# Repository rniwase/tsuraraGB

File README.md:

# tsuraraGB
Nintendo Gameboy cartridge-shaped FPGA (Lattice iCE40UP5K) development board

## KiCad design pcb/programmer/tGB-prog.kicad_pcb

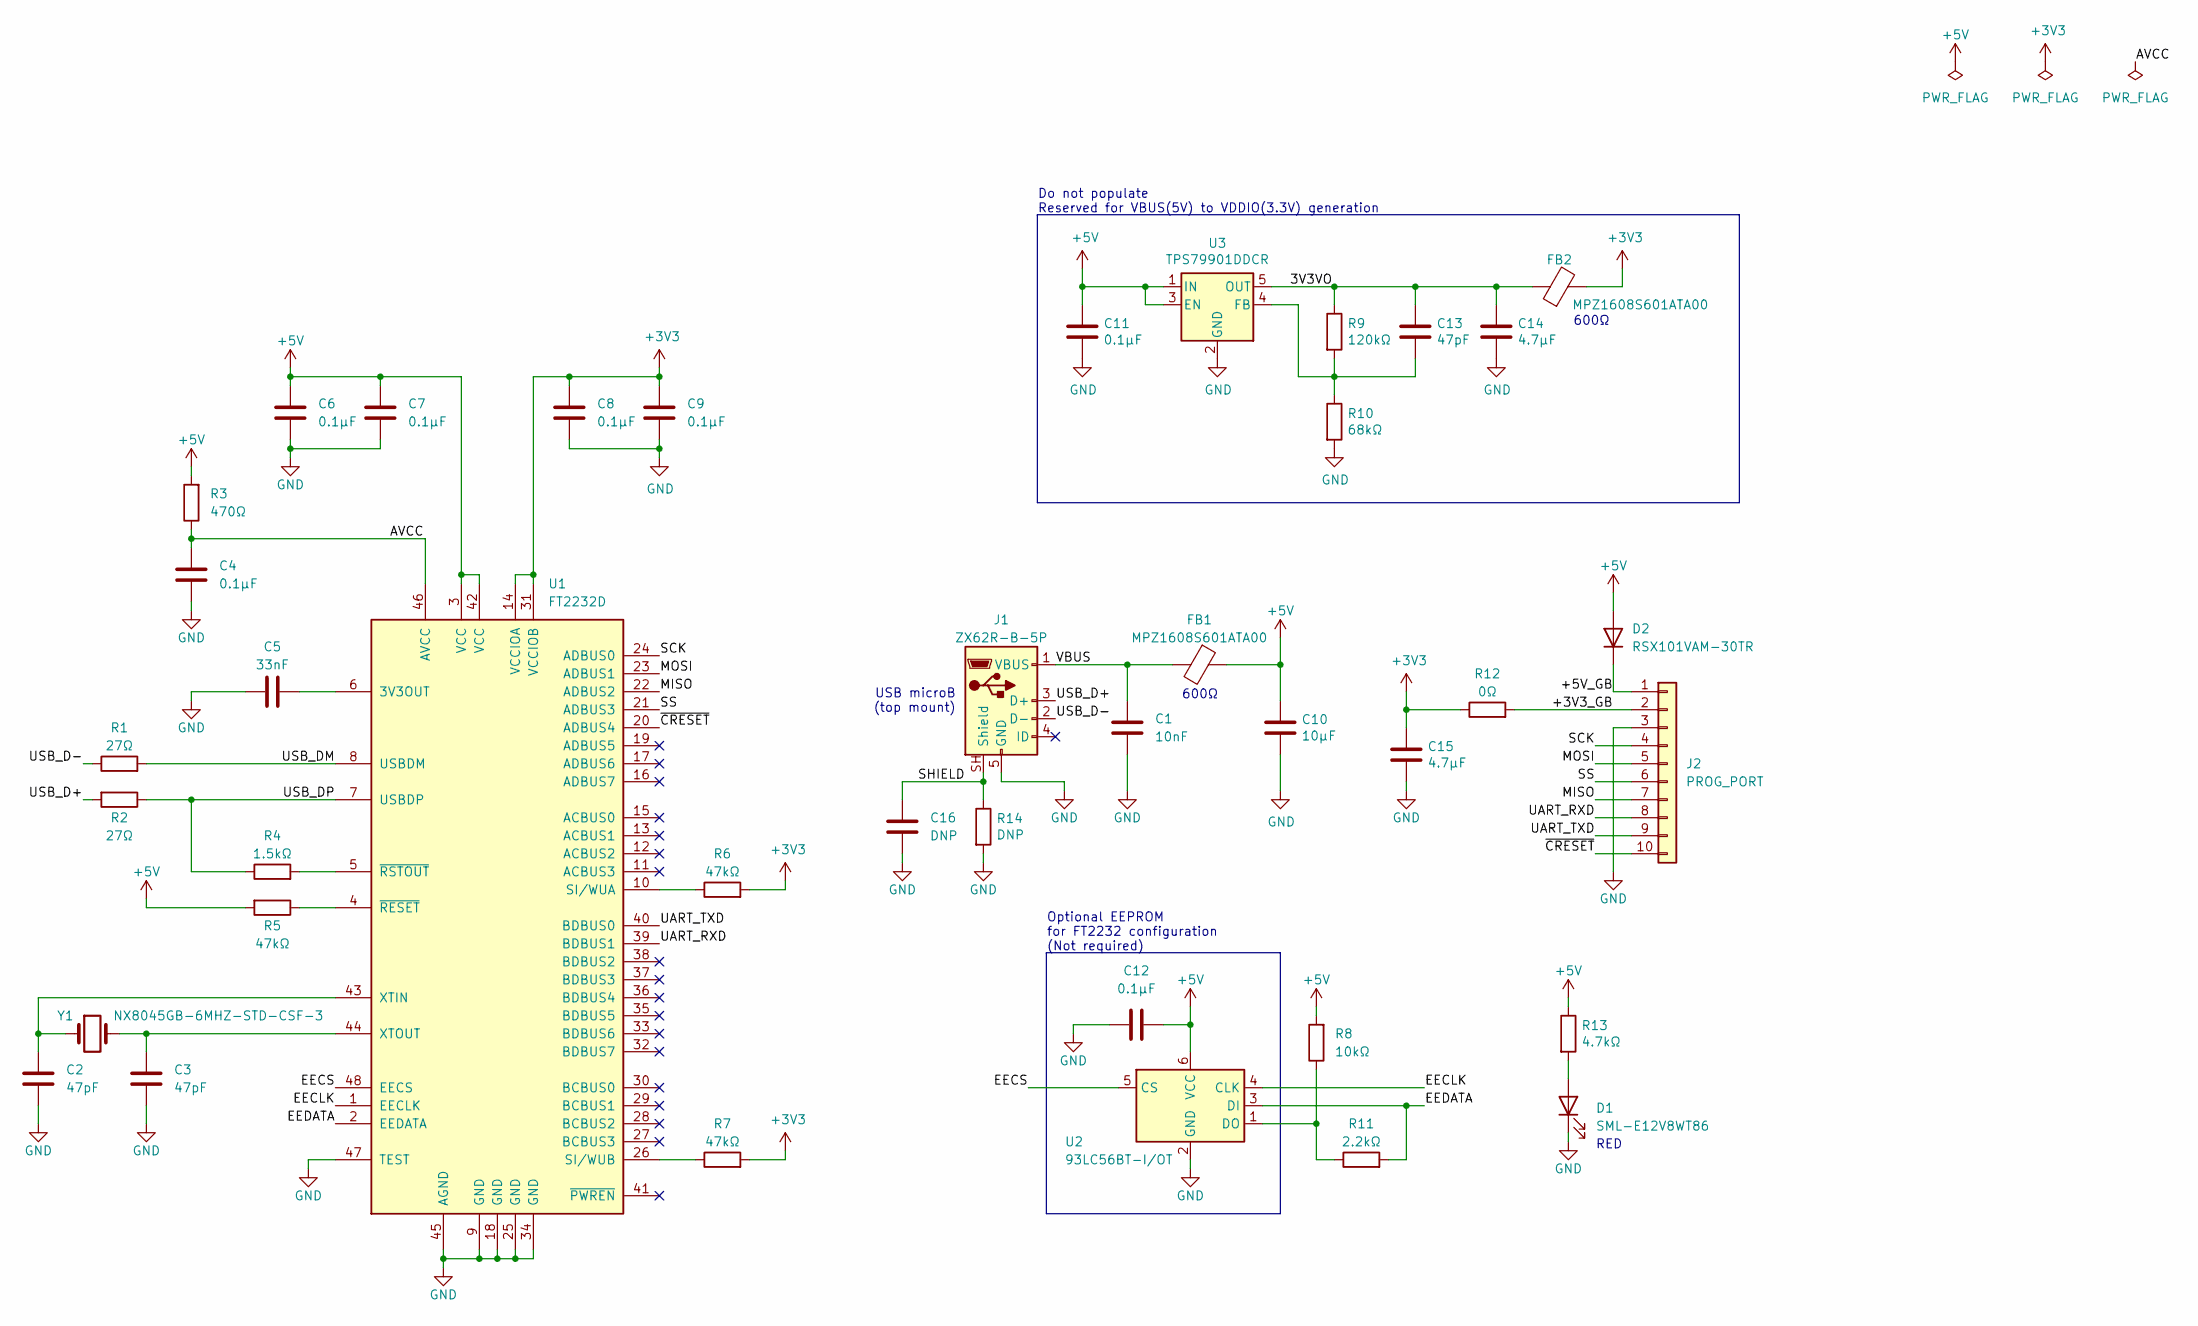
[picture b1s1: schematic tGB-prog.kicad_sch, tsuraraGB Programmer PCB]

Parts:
C1: 10nF; C_0402_1005Metric
C2, C3, C13: 47pF; C_0402_1005Metric
C4, C6, C7, C8, C9, C11, C12: 0.1μF; C_0402_1005Metric
C5: 33nF; C_0402_1005Metric
C10: 10μF; C_0603_1608Metric
C14: 4.7μF; C_0402_1005Metric
C15: 4.7μF; C_0603_1608Metric
C16: DNP; C_0402_1005Metric
D1: SML-E12V8WT86; LED_0603_1608Metric_Castellated
D2: RSX101VAM-30TR; D_TUMD2
FB1, FB2: MPZ1608S601ATA00; L_0603_1608Metric
J1: ZX62R-B-5P
J2: PROG_PORT; PinSocket_1x10_P2.54_Sidemount
R1, R2: 27Ω; R_0402_1005Metric
R3: 470Ω; R_0402_1005Metric
R4: 1.5kΩ; R_0402_1005Metric
R5, R6, R7: 47kΩ; R_0402_1005Metric
R8: 10kΩ; R_0402_1005Metric
R9: 120kΩ; R_0402_1005Metric
R10: 68kΩ; R_0402_1005Metric
R11: 2.2kΩ; R_0402_1005Metric
R12: 0Ω; R_0603_1608Metric
R13: 4.7kΩ; R_0402_1005Metric
R14: DNP; R_0402_1005Metric
U1: FT2232D; LQFP-48_7x7mm_P0.5mm
U2: 93LC56BT-I/OT; SOT-23-6
U3: TPS79901DDCR; SOT-23-5
Y1: NX8045GB-6MHZ-STD-CSF-3; Crystal_SMD_TXC_AX_8045-2Pin_8.0x4.5mm

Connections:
+3V3: C8.1, C9.1, C15.1, FB2.2, R6.2, R7.2, R12.1, U1.14 (VCCIOA), U1.31 (VCCIOB)
+5V: C6.1, C7.1, C10.1, C11.1, C12.2, D2.2 (A), FB1.1, R3.2, R5.2, R8.2, R13.1, U1.3 (VCC), U1.42 (VCC), U2.6 (VCC), U3.1 (IN), U3.3 (EN)
/3V3VO: C13.1, C14.1, FB2.1, R9.1, U3.5 (OUT)
/+3V3_GB: J2.2, R12.2
/+5V_GB: D2.1 (K), J2.1
/AVCC: C4.1, R3.1, U1.46 (AVCC)
/EECLK: U1.1 (EECLK), U2.4 (CLK)
/EECS: U1.48 (EECS), U2.5 (CS)
/EEDATA: R11.2, U1.2 (EEDATA), U2.3 (DI)
/MISO: J2.7, U1.22 (ADBUS2)
/MOSI: J2.5, U1.23 (ADBUS1)
/SCK: J2.4, U1.24 (ADBUS0)
/SHIELD: C16.1, J1.SH (Shield), R14.1
/SS: J2.6, U1.21 (ADBUS3)
/UART_RXD: J2.8, U1.39 (BDBUS1)
/UART_TXD: J2.9, U1.40 (BDBUS0)
/USB_D+: J1.3 (D+), R2.2
/USB_D-: J1.2 (D-), R1.1
/USB_DM: R1.2, U1.8 (USBDM)
/USB_DP: R2.1, R4.1, U1.7 (USBDP)
/VBUS: C1.1, FB1.2, J1.1 (VBUS)
/~CRESET: J2.10, U1.20 (ADBUS4)
GND: C1.2, C2.2, C3.2, C4.2, C5.1, C6.2, C7.2, C8.2, C9.2, C10.2, C11.2, C12.1, C14.2, C15.2, C16.2, D1.1 (K), J1.5 (GND), J2.3, R10.2, R14.2, U1.9 (GND), U1.18 (GND), U1.25 (GND), U1.34 (GND), U1.45 (AGND), U1.47 (TEST), U2.2 (GND), U3.2 (GND)
unnamed: D1.2 (A), R13.2
unnamed: C5.2, U1.6 (3V3OUT)
unnamed: R6.1, U1.10 (SI/WUA)
unnamed: R7.1, U1.26 (SI/WUB)
unnamed: C2.1, U1.43 (XTIN), Y1.1
unnamed: C3.1, U1.44 (XTOUT), Y1.2
unnamed: R5.1, U1.4 (~RESET)
unnamed: R4.2, U1.5 (~RSTOUT)
unnamed: R8.1, R11.1, U2.1 (DO)
unnamed: C13.2, R9.2, R10.1, U3.4 (FB)

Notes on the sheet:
600Ω
USB microB (top mount)
RED
Do not populate Reserved for VBUS(5V) to VDDIO(3.3V) generation
Optional EEPROM for FT2232 configuration (Not required)

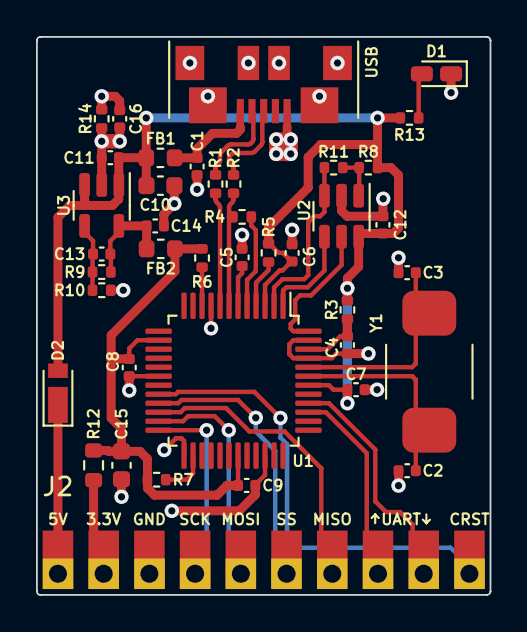
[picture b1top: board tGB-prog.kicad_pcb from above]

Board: 2 copper layers, 25.2 x 31.0 mm, 40 parts (0 on the bottom side), 33 nets.

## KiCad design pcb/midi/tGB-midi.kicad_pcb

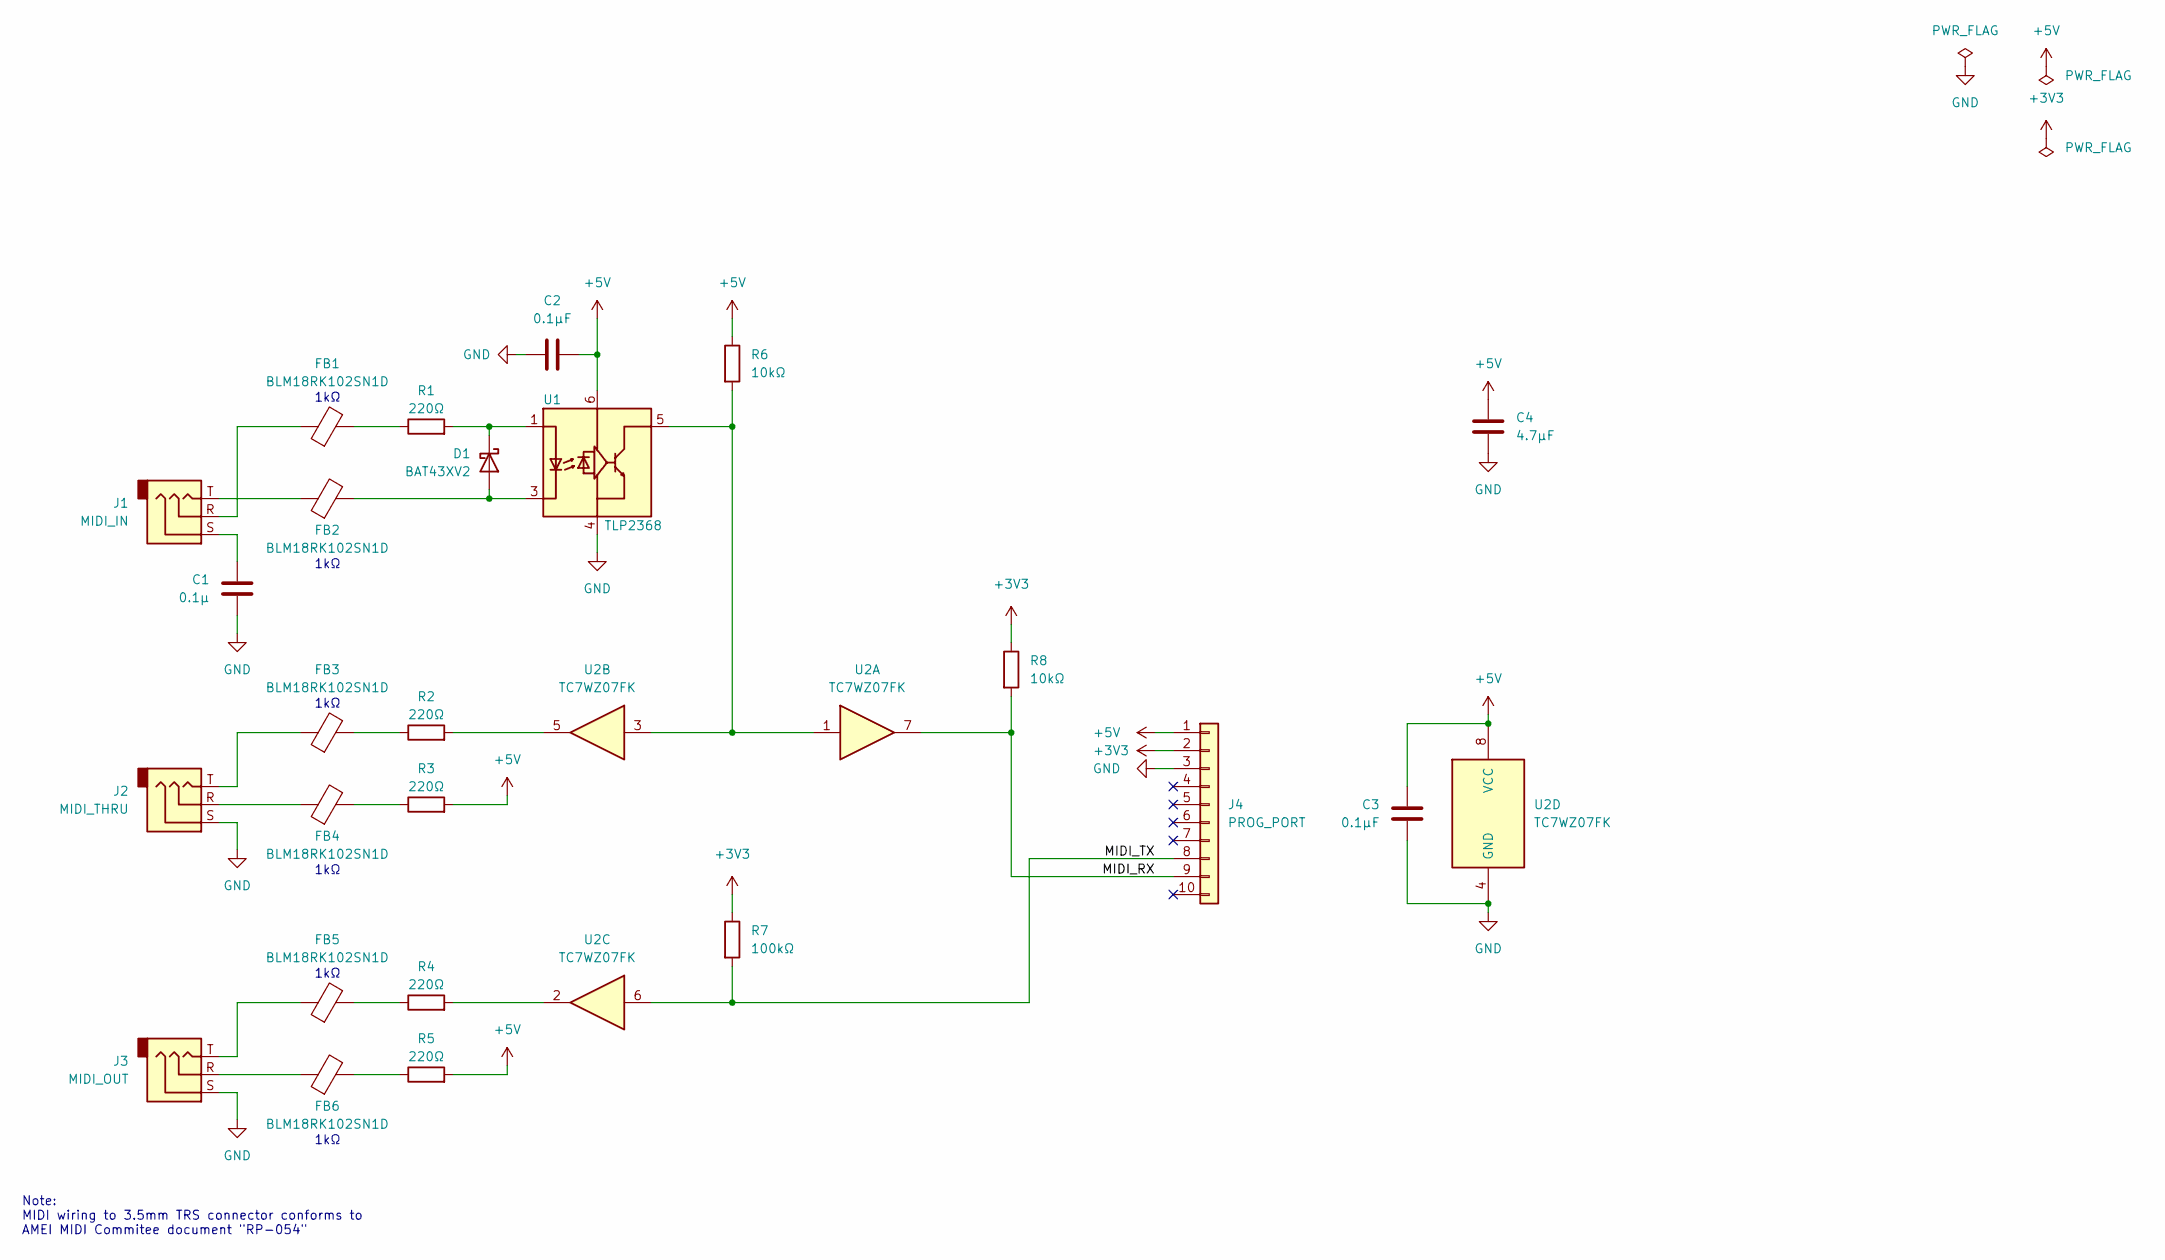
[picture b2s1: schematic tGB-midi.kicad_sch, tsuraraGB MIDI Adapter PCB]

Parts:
C1: 0.1μ; C_0402_1005Metric
C2, C3: 0.1μF; C_0402_1005Metric
C4: 4.7μF; C_0402_1005Metric
D1: BAT43XV2; D_SOD-523
FB1, FB2, FB3, FB4, FB5, FB6: BLM18RK102SN1D; L_0603_1608Metric
J1: MIDI_IN; MJ-8435
J2: MIDI_THRU; MJ-8435
J3: MIDI_OUT; MJ-8435
J4: PROG_PORT; PinSocket_1x10_P2.54_Sidemount
R1, R2, R3, R4, R5: 220Ω; R_0402_1005Metric
R6, R8: 10kΩ; R_0402_1005Metric
R7: 100kΩ; R_0402_1005Metric
U1: TLP2368; SO-5_4.4x3.6mm_P1.27mm
U2: TC7WZ07FK; VSSOP-8_2.3x2mm_P0.5mm

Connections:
+3V3: J4.2, R7.1, R8.1
+5V: C2.2, C3.2, C4.1, J4.1, R3.2, R5.2, R6.1, U1.6 (VDD), U2.8 (VCC)
/MIDI_RX: J4.9, R8.2, U2.7
/MIDI_TX: J4.8, R7.2, U2.6
GND: C1.1, C2.1, C3.1, C4.2, J2.S, J3.S, J4.3, U1.4 (GND), U2.4 (GND)
unnamed: C1.2, J1.S
unnamed: D1.2 (A), FB2.2, U1.3 (K)
unnamed: D1.1 (K), R1.2, U1.1 (A)
unnamed: FB1.1, J1.R
unnamed: FB1.2, R1.1
unnamed: FB2.1, J1.T
unnamed: FB3.1, J2.T
unnamed: FB3.2, R2.1
unnamed: FB4.1, J2.R
unnamed: FB4.2, R3.1
unnamed: FB5.1, J3.T
unnamed: FB5.2, R4.1
unnamed: FB6.1, J3.R
unnamed: FB6.2, R5.1
unnamed: R2.2, U2.5
unnamed: R4.2, U2.2
unnamed: R6.2, U1.5 (VO), U2.1, U2.3

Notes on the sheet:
1kΩ
Note: MIDI wiring to 3.5mm TRS connector conforms to AMEI MIDI Commitee document "RP-054"

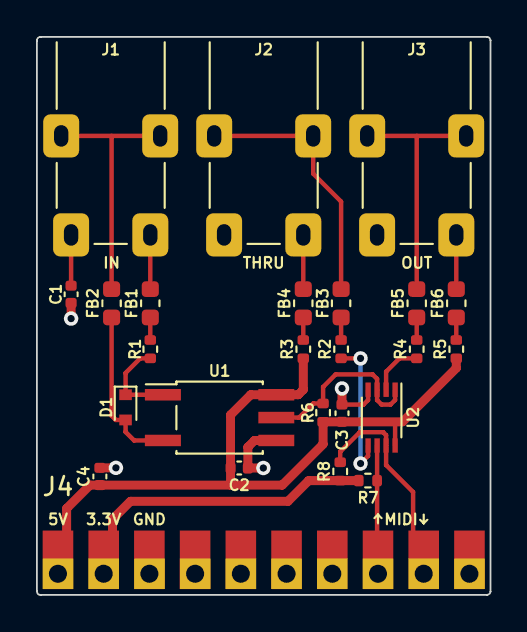
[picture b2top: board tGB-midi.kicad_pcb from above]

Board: 2 copper layers, 25.2 x 31.0 mm, 25 parts (0 on the bottom side), 22 nets.

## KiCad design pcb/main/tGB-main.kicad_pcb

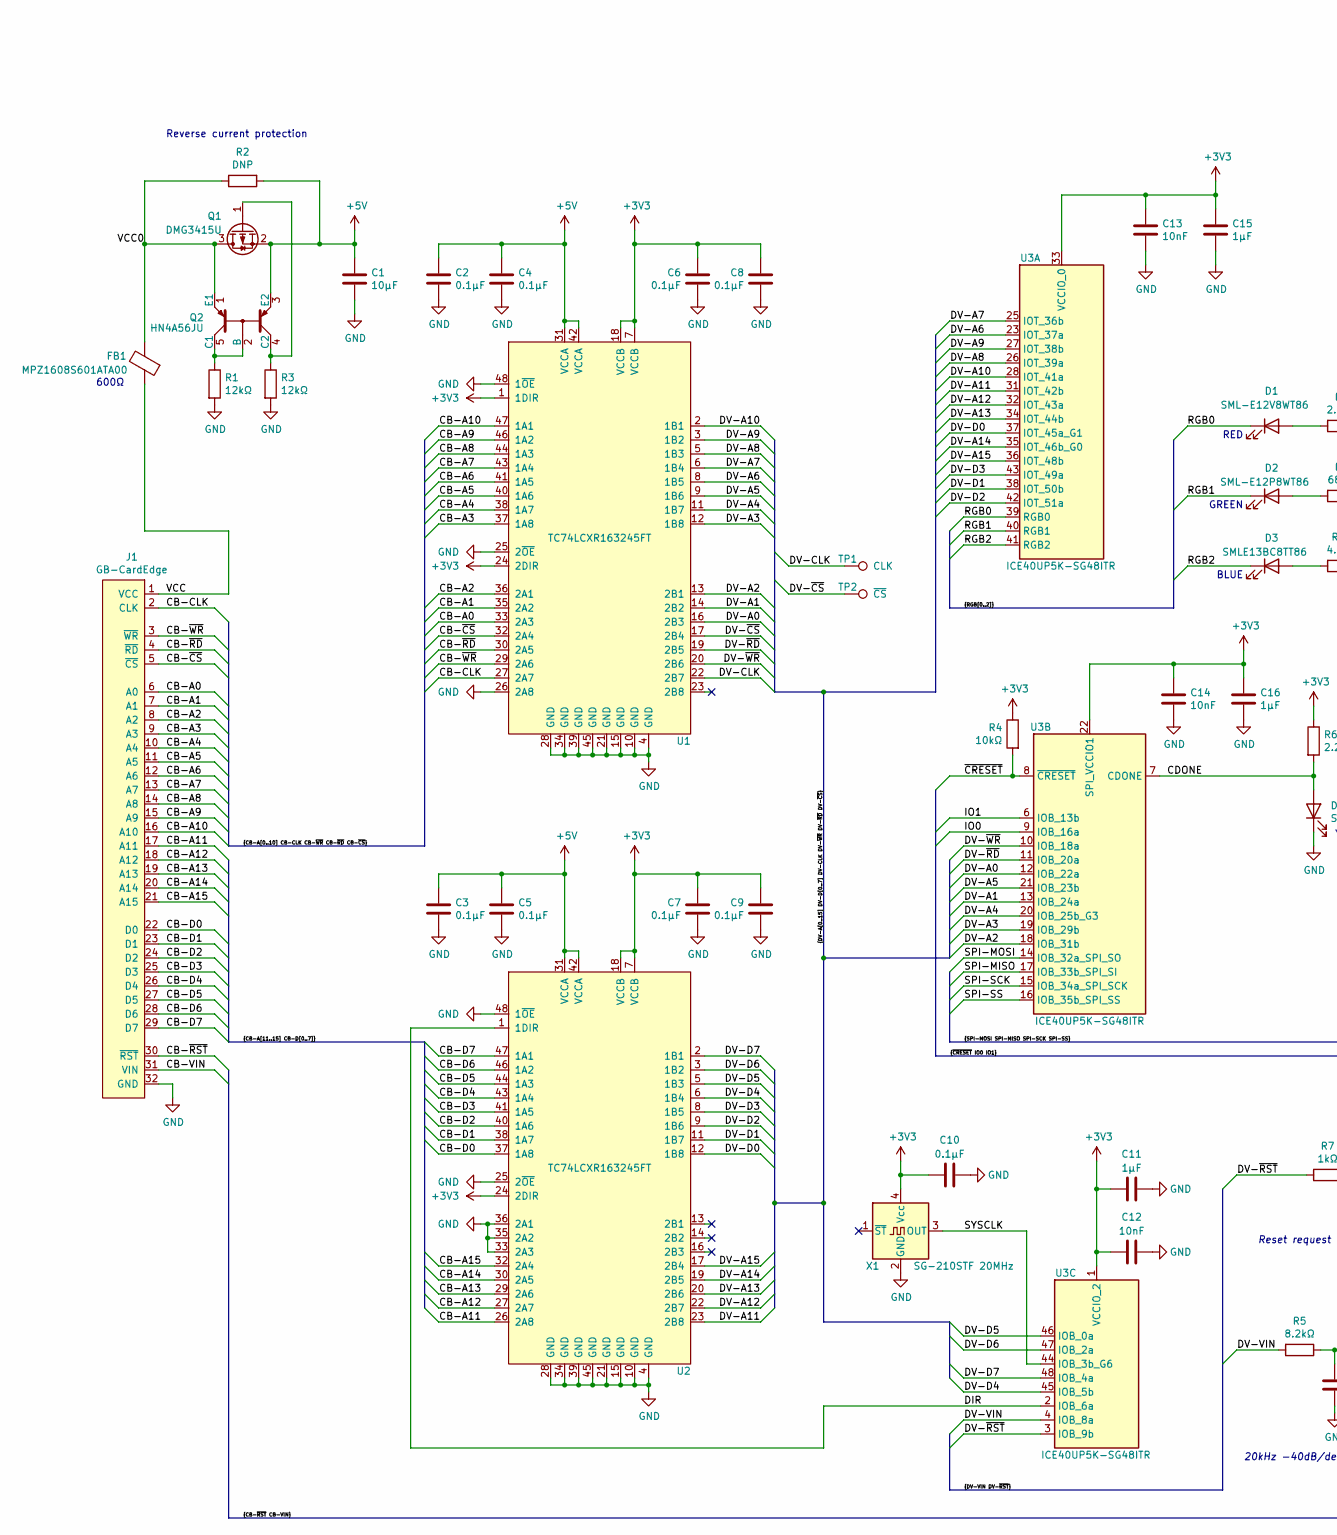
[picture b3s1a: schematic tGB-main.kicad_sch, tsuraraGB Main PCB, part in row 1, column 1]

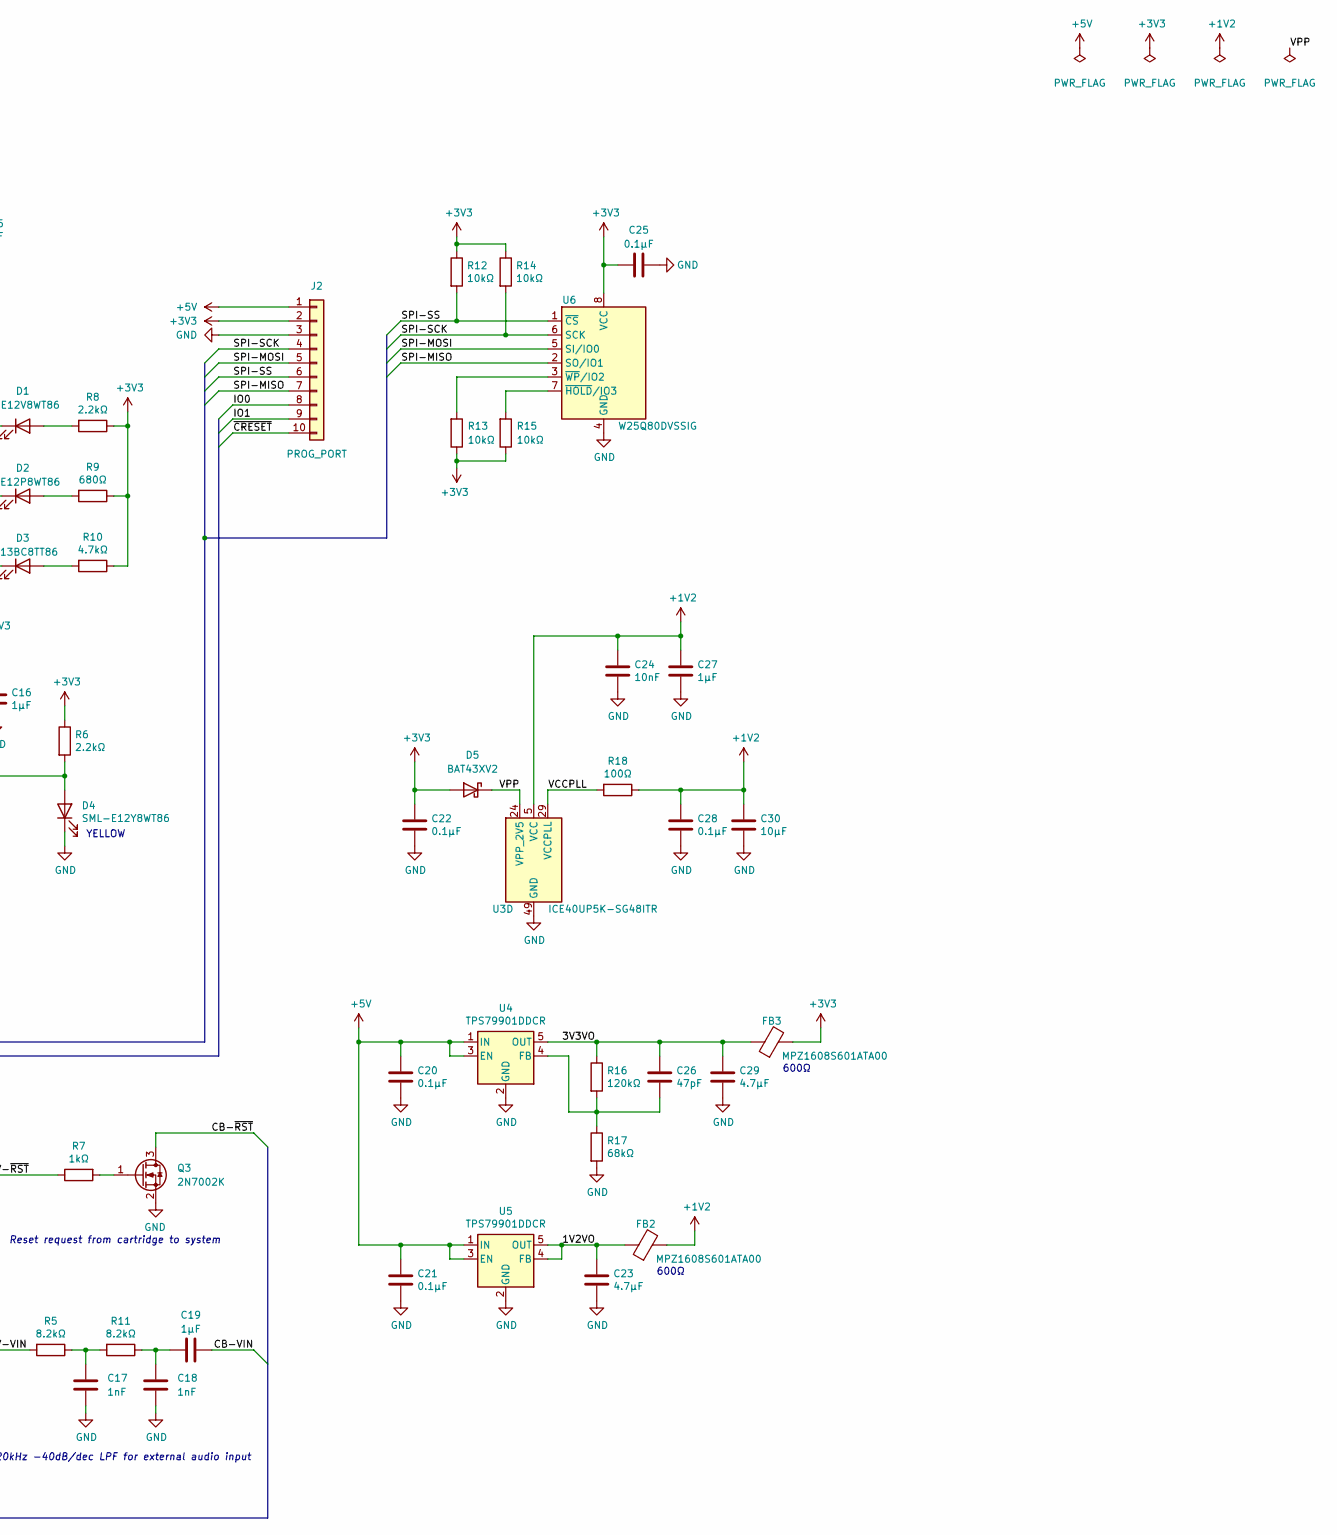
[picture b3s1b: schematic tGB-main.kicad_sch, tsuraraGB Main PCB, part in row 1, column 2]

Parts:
C1, C30: 10μF; C_0603_1608Metric
C2, C3, C4, C5, C6, C7, C8, C9, C10, C20, C21, C22, C25, C28: 0.1μF; C_0402_1005Metric
C11, C15, C16, C19, C27: 1μF; C_0402_1005Metric
C12, C13, C14, C24: 10nF; C_0402_1005Metric
C17, C18: 1nF; C_0402_1005Metric
C23, C29: 4.7μF; C_0402_1005Metric
C26: 47pF; C_0402_1005Metric
D1: SML-E12V8WT86; LED_0603_1608Metric_Castellated
D2: SML-E12P8WT86; LED_0603_1608Metric_Castellated
D3: SMLE13BC8TT86; LED_0603_1608Metric_Castellated
D4: SML-E12Y8WT86; LED_0603_1608Metric_Castellated
D5: BAT43XV2; D_SOD-523
FB1, FB2, FB3: MPZ1608S601ATA00; L_0603_1608Metric
J1: GB-CardEdge
J2: PROG_PORT; PinHeader_1x10_P2.54_Sidemount
Q1: DMG3415U; SOT-23
Q2: HN4A56JU; SOT-353_SC-70-5
Q3: 2N7002K; SOT-23
R1, R3: 12kΩ; R_0402_1005Metric
R2: DNP; R_0603_1608Metric
R4, R12, R13, R14, R15: 10kΩ; R_0402_1005Metric
R5, R11: 8.2kΩ; R_0402_1005Metric
R6, R8: 2.2kΩ; R_0402_1005Metric
R7: 1kΩ; R_0402_1005Metric
R9: 680Ω; R_0402_1005Metric
R10: 4.7kΩ; R_0402_1005Metric
R16: 120kΩ; R_0402_1005Metric
R17: 68kΩ; R_0402_1005Metric
R18: 100Ω; R_0402_1005Metric
TP1: CLK; TestPoint_Pad_D1.0mm
TP2: ~{CS}; TestPoint_Pad_D1.0mm
U1, U2: TC74LCXR163245FT; TSSOP-48_6.1x12.5mm_P0.5mm
U3: ICE40UP5K-SG48ITR; QFN-48-1EP_7x7mm_P0.5mm_EP5.6x5.6mm
U4, U5: TPS79901DDCR; SOT-23-5
U6: W25Q80DVSSIG; SOIC-8_5.3x5.3mm_P1.27mm
X1: SG-210STF 20MHz; Oscillator_SMD_SeikoEpson_SG210-4Pin_2.5x2.0mm

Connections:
+1V2: C24.1, C27.1, C28.1, C30.1, FB2.2, R18.1, U3.5 (VCC), U3.30 (VCC)
+3V3: C6.1, C7.1, C8.1, C9.1, C10.1, C11.1, C12.1, C13.1, C14.1, C15.1, C16.1, C22.1, C25.1, D5.2 (A), FB3.2, J2.2, R4.1, R6.1, R8.1, R9.1, R10.1, R12.1, R13.1, R14.1, R15.1, U1.1 (1DIR), U1.7 (VCCB), U1.18 (VCCB), U1.24 (2DIR), U2.7 (VCCB), U2.18 (VCCB), U2.24 (2DIR), U3.1 (VCCIO_2), U3.22 (SPI_VCCIO1), U3.33 (VCCIO_0), U6.8 (VCC), X1.4 (Vcc)
+5V: C1.1, C2.1, C3.1, C4.1, C5.1, C20.1, C21.1, J2.1, Q1.2 (S), Q2.3 (E2), R2.2, U1.31 (VCCA), U1.42 (VCCA), U2.31 (VCCA), U2.42 (VCCA), U4.1 (IN), U4.3 (EN), U5.1 (IN), U5.3 (EN)
/1V2VO: C23.1, FB2.1, U5.4 (FB), U5.5 (OUT)
/3V3VO: C26.1, C29.1, FB3.1, R16.1, U4.5 (OUT)
/CB-A0: J1.6 (A0), U1.33 (2A3)
/CB-A1: J1.7 (A1), U1.35 (2A2)
/CB-A2: J1.8 (A2), U1.36 (2A1)
/CB-A3: J1.9 (A3), U1.37 (1A8)
/CB-A4: J1.10 (A4), U1.38 (1A7)
/CB-A5: J1.11 (A5), U1.40 (1A6)
/CB-A6: J1.12 (A6), U1.41 (1A5)
/CB-A7: J1.13 (A7), U1.43 (1A4)
/CB-A8: J1.14 (A8), U1.44 (1A3)
/CB-A9: J1.15 (A9), U1.46 (1A2)
/CB-A10: J1.16 (A10), U1.47 (1A1)
/CB-A11: J1.17 (A11), U2.26 (2A8)
/CB-A12: J1.18 (A12), U2.27 (2A7)
/CB-A13: J1.19 (A13), U2.29 (2A6)
/CB-A14: J1.20 (A14), U2.30 (2A5)
/CB-A15: J1.21 (A15), U2.32 (2A4)
/CB-CLK: J1.2 (CLK), U1.27 (2A7)
/CB-D0: J1.22 (D0), U2.37 (1A8)
/CB-D1: J1.23 (D1), U2.38 (1A7)
/CB-D2: J1.24 (D2), U2.40 (1A6)
/CB-D3: J1.25 (D3), U2.41 (1A5)
/CB-D4: J1.26 (D4), U2.43 (1A4)
/CB-D5: J1.27 (D5), U2.44 (1A3)
/CB-D6: J1.28 (D6), U2.46 (1A2)
/CB-D7: J1.29 (D7), U2.47 (1A1)
/CB-VIN: C19.1, J1.31 (VIN)
/CB-~CS: J1.5 (~CS), U1.32 (2A4)
/CB-~RD: J1.4 (~RD), U1.30 (2A5)
/CB-~RST: J1.30 (~RST), Q3.3 (D)
/CB-~WR: J1.3 (~WR), U1.29 (2A6)
/CDONE: D4.2 (A), R6.2, U3.7 (CDONE)
/DIR: U2.1 (1DIR), U3.2 (IOB_6a)
/DV-A0: U1.16 (2B3), U3.12 (IOB_22a)
/DV-A1: U1.14 (2B2), U3.13 (IOB_24a)
/DV-A2: U1.13 (2B1), U3.18 (IOB_31b)
/DV-A3: U1.12 (1B8), U3.19 (IOB_29b)
/DV-A4: U1.11 (1B7), U3.20 (IOB_25b_G3)
/DV-A5: U1.9 (1B6), U3.21 (IOB_23b)
/DV-A6: U1.8 (1B5), U3.23 (IOT_37a)
/DV-A7: U1.6 (1B4), U3.25 (IOT_36b)
/DV-A8: U1.5 (1B3), U3.26 (IOT_39a)
/DV-A9: U1.3 (1B2), U3.27 (IOT_38b)
/DV-A10: U1.2 (1B1), U3.28 (IOT_41a)
/DV-A11: U2.23 (2B8), U3.31 (IOT_42b)
/DV-A12: U2.22 (2B7), U3.32 (IOT_43a)
/DV-A13: U2.20 (2B6), U3.34 (IOT_44b)
/DV-A14: U2.19 (2B5), U3.35 (IOT_46b_G0)
/DV-A15: U2.17 (2B4), U3.36 (IOT_48b)
/DV-CLK: TP1.1 (1_1), U1.22 (2B7)
/DV-D0: U2.12 (1B8), U3.37 (IOT_45a_G1)
/DV-D1: U2.11 (1B7), U3.38 (IOT_50b)
/DV-D2: U2.9 (1B6), U3.42 (IOT_51a)
/DV-D3: U2.8 (1B5), U3.43 (IOT_49a)
/DV-D4: U2.6 (1B4), U3.45 (IOB_5b)
/DV-D5: U2.5 (1B3), U3.46 (IOB_0a)
/DV-D6: U2.3 (1B2), U3.47 (IOB_2a)
/DV-D7: U2.2 (1B1), U3.48 (IOB_4a)
/DV-VIN: R5.2, U3.4 (IOB_8a)
/DV-~CS: TP2.1 (1_1), U1.17 (2B4)
/DV-~RD: U1.19 (2B5), U3.11 (IOB_20a)
/DV-~RST: R7.1, U3.3 (IOB_9b)
/DV-~WR: U1.20 (2B6), U3.10 (IOB_18a)
/IO0: J2.8, U3.9 (IOB_16a)
/IO1: J2.9, U3.6 (IOB_13b)
/RGB0: D1.1 (K), U3.39 (RGB0)
/RGB1: D2.1 (K), U3.40 (RGB1)
/RGB2: D3.1 (K), U3.41 (RGB2)
/SPI-MISO: J2.7, U3.17 (IOB_33b_SPI_SI), U6.2 (SO/IO1)
/SPI-MOSI: J2.5, U3.14 (IOB_32a_SPI_SO), U6.5 (SI/IO0)
/SPI-SCK: J2.4, R14.2, U3.15 (IOB_34a_SPI_SCK), U6.6 (SCK)
/SPI-SS: J2.6, R12.2, U3.16 (IOB_35b_SPI_SS), U6.1 (~CS)
/SYSCLK: U3.44 (IOB_3b_G6), X1.3 (OUT)
/VCC: FB1.1, J1.1 (VCC)
/VCC0: FB1.2, Q1.3 (D), Q2.1 (E1), R2.1
/VCCPLL: R18.2, U3.29 (VCCPLL)
/VPP: D5.1 (K), U3.24 (VPP_2V5)
/~CRESET: J2.10, R4.2, U3.8 (~CRESET)
GND: C1.2, C2.2, C3.2, C4.2, C5.2, C6.2, C7.2, C8.2, C9.2, C10.2, C11.2, C12.2, C13.2, C14.2, C15.2, C16.2, C17.2, C18.2, C20.2, C21.2, C22.2, C23.2, C24.2, C25.2, C27.2, C28.2, C29.2, C30.2, D4.1 (K), J1.32 (GND), J2.3, Q3.2 (S), R1.2, R3.2, R17.2, U1.4 (GND), U1.10 (GND), U1.15 (GND), U1.21 (GND), U1.25 (2~OE), U1.26 (2A8), U1.28 (GND), U1.34 (GND), U1.39 (GND), U1.45 (GND), U1.48 (1~OE), U2.4 (GND), U2.10 (GND), U2.15 (GND), U2.21 (GND), U2.25 (2~OE), U2.28 (GND), U2.33 (2A3), U2.34 (GND), U2.35 (2A2), U2.36 (2A1), U2.39 (GND), U2.45 (GND), U2.48 (1~OE), U3.49 (GND), U4.2 (GND), U5.2 (GND), U6.4 (GND), X1.2 (GND)
unnamed: C17.1, R5.1, R11.2
unnamed: C18.1, C19.2, R11.1
unnamed: D1.2 (A), R8.2
unnamed: D2.2 (A), R9.2
unnamed: D3.2 (A), R10.2
unnamed: Q1.1 (G), Q2.4 (C2), R3.1
unnamed: Q2.2 (B), Q2.5 (C1), R1.1
unnamed: Q3.1 (G), R7.2
unnamed: C26.2, R16.2, R17.1, U4.4 (FB)
unnamed: R15.2, U6.7 (~HOLD/IO3)
unnamed: R13.2, U6.3 (~WP/IO2)

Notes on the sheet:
GREEN
600Ω
YELLOW
RED
Reverse current protection
Reset request from cartridge to system
BLUE
20kHz -40dB/dec LPF for external audio input

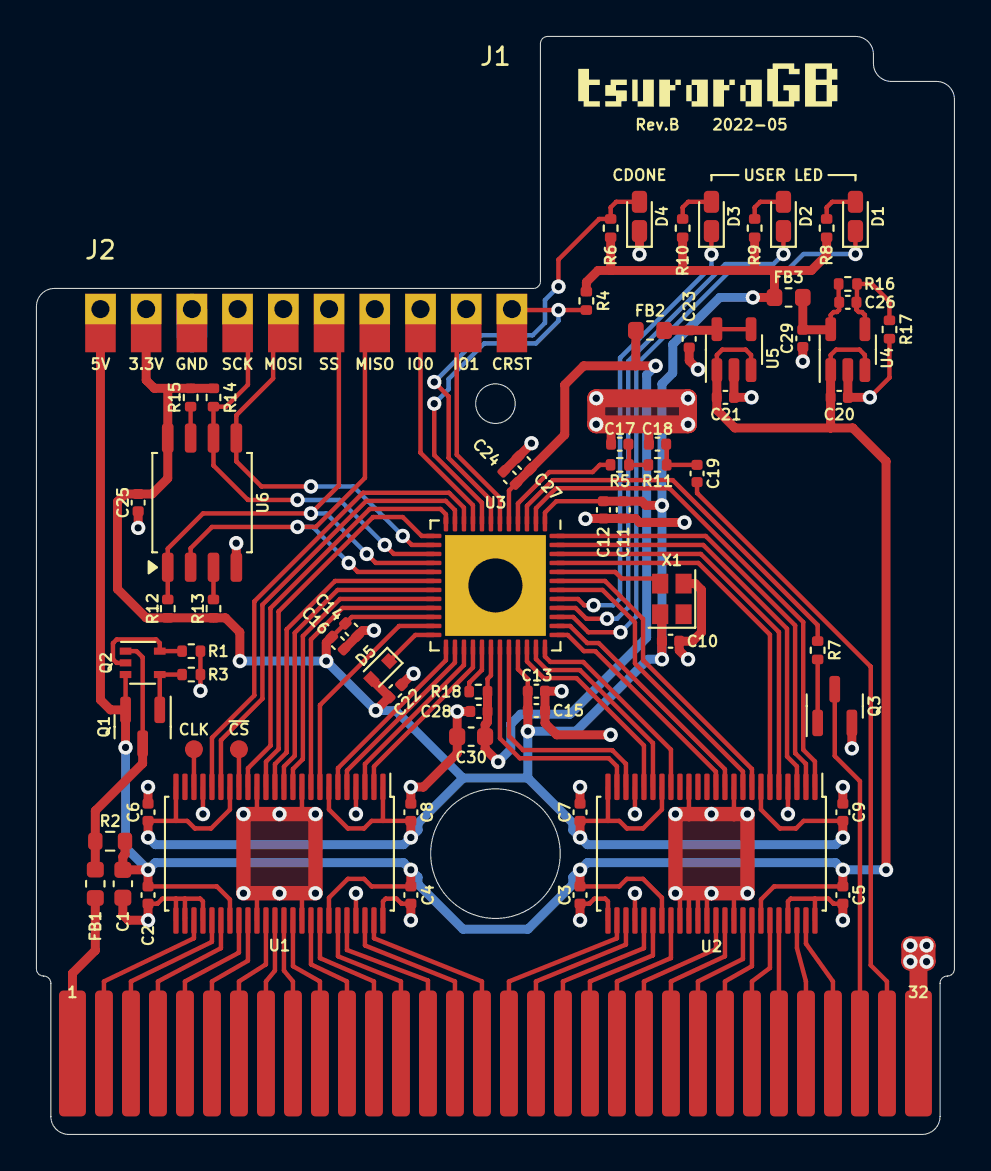
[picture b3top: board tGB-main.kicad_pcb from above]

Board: 2 copper layers, 51.0 x 61.0 mm, 70 parts (0 on the bottom side), 94 nets.

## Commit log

2020-12-08 modify value fields
2020-12-08 modify decoup C value
2020-12-10 modify README
2020-12-10 change value of X1
2020-12-11 add .gitattributes
2020-12-13 add sample (wip)
2020-12-13 fix comment
2020-12-15 update sample
2020-12-15 rename directory
2020-12-16 update LED current limiting resistors
2020-12-16 swap C11 C14 value
2020-12-18 correct number of banks
2021-08-10 add midi_sound_gen
2022-05-05 migrate to KiCAD 6.0
2022-05-07 support for gbdk-2020 v4.0.6
2022-05-07 replace X1 parts on schematic
2022-05-07 update schematic, change Lx to FBx, add LPF circuit for Vin, reselection of some components
2022-05-08 update pcb wip
2022-05-08 update pcb, drc ok
2022-05-09 update board setup
2022-05-14 change pin headers to THT, tweaking placement
2022-05-14 add mounting hole
2022-05-15 update illustration
2022-05-17 add reverse current protection circuit between VCC and 5V, remove mounthole
2022-05-19 update cardedge
2022-05-19 rename project
2022-05-19 rename project, update pcb
2022-05-19 fix typo
2022-06-12 update R16,R17 value
2022-06-16 common RTL files, update Makefile
2022-07-18 add midi extension pcb
2022-07-18 common symbols and footprints
2022-08-27 add programmer pcb (wip)
2022-08-29 update pcb (wip)
2022-09-09 add programmer script
2022-09-16 replace FT232H with FT2232D to use UART in secondary
2022-09-16 complete placement and route of components, DRC passed with warnings
2022-09-16 fix silkscreens
2022-09-17 add silkscreen of board name
2022-09-24 axis origin and plot setup
2022-09-24 fix D+ and D- polarity reversal on USB
2022-09-24 change C4 value from 10uF to 4.7uF
2022-09-25 change Y1 parts, centering of USB connector
2022-09-25 add junpers for VDDIO supply from main board, add power LED
2022-09-25 separate USB GND and shield
2022-09-25 optimize GND and shield zone, fillet USB data tracks
2022-09-29 fix EOL
2022-09-29 rename directories
2022-09-29 rename directories, update create_project.tcl
2022-10-01 add comments
2022-10-01 add comment, fix power net name
2022-10-01 set title and revision
2023-01-12 support for yosys/nextpnr
2023-01-12 add install_ubuntu.sh
2023-01-19 optimize midi_sound_gen RTLs
2023-01-19 rename software, update gitignore
2023-03-11 optimize RTLs
2023-03-11 eliminate build_option.sv, add primitive module wrapper
2023-03-12 add description
2023-03-13 add newline at eol
2023-03-14 support for multiple channels, wip
2023-03-16 support for wave channel
2023-09-10 update build dependencies
2023-12-29 add Backpanel draft
2024-01-03 add workflow for build verification of examples
2024-01-03 add paths to workflow
2024-01-03 add workflow for ERC/DRC
2024-01-04 migration from KiCad 6 to 7
2024-01-04 update workflows
2024-01-04 remove workflow check-pcb
2026-04-14 examples: migrate gateware build environment to OSS CAD Suite, update Makefile, programmer scripts
2026-04-14 rom_bank_demo: rename from mbc_128k_rom, update software for GBDK 4.5.0
2026-04-14 midi_sound_gen: update for OSS CAD Suite 20260412 and GBDK 4.5.0
2026-04-14 remove github workflows
2026-04-28 examples: add multiplier_demo
2026-05-09 Update LICENSE
2026-05-09 mac.sv: add parameter sign
2026-05-09 offload frequency table to gateware, add pitch bend and volume control, fix MIDI parser for handling system messages
2026-05-19 refactor MIDI RTLs, add all notes off feature, add MIDI RTL simulations
2026-05-19 formatting RTLs
2026-05-20 wip: add MIDI modwheel, pan, gp1 control
2026-05-20 wip: add build support for linux aarch64
2026-05-20 wip: add build support for macos
2026-05-20 fix indent space
2026-05-20 fix prepare/build target
2026-05-20 fix instance name
2026-05-20 fix for statement
2026-05-21 wip: add windows build support
2026-05-29 wip: add control changes (modwheel, pan, gp1)
2026-05-31 add pan and duty ratio control
2026-06-16 migrate KiCad 7 -> 10
